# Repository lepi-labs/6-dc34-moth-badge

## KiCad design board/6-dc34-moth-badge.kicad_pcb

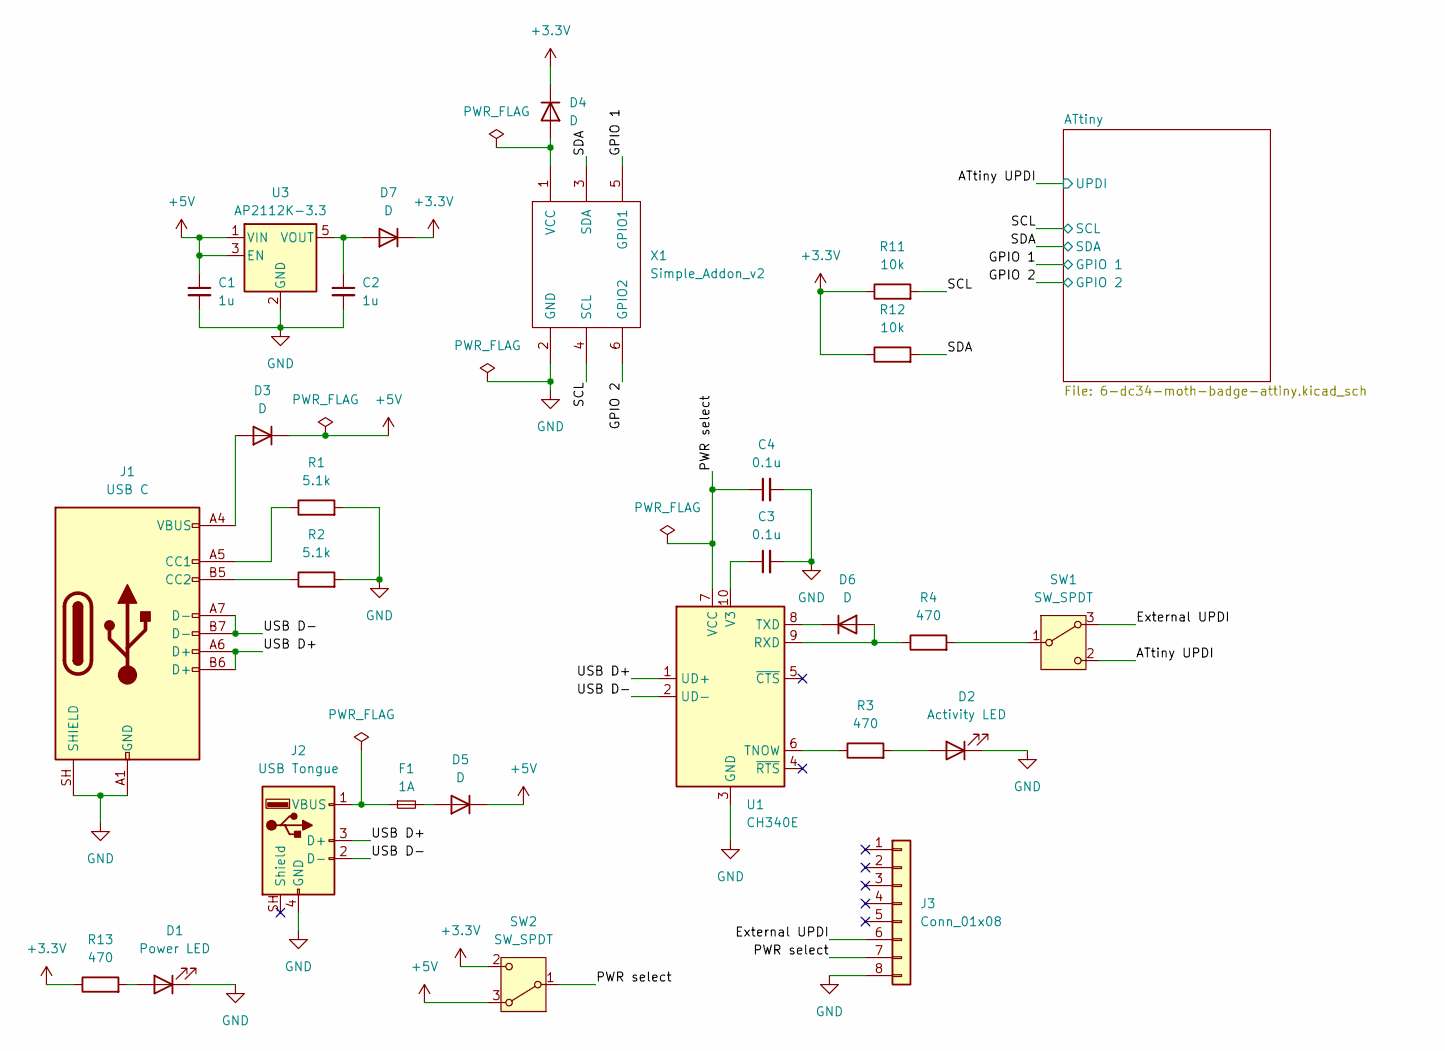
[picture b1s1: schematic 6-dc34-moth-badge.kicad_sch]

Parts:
C1, C2: 1u; C_1206_3216Metric_Pad1.33x1.80mm_HandSolder
C3, C4: 0.1u; C_1206_3216Metric_Pad1.33x1.80mm_HandSolder
D1: Power LED; LED_1206_3216Metric_Pad1.42x1.75mm_HandSolder
D2: Activity LED; LED_1206_3216Metric_Pad1.42x1.75mm_HandSolder
D3, D4, D5, D6, D7: D; D_1206_3216Metric_Pad1.42x1.75mm_HandSolder
F1: 1A; Fuse_1206_3216Metric_Pad1.42x1.75mm_HandSolder
J1: USB C; USB421603A
J2: USB Tongue; USB_Tongue
J3: Conn_01x08; PinHeader_1x08_P2.54mm_Vertical
R1, R2: 5.1k; R_1206_3216Metric_Pad1.30x1.75mm_HandSolder
R3, R4, R13: 470; R_1206_3216Metric_Pad1.30x1.75mm_HandSolder
R11, R12: 10k; R_1206_3216Metric_Pad1.30x1.75mm_HandSolder
SW1, SW2: SW_SPDT; SLW882292SMTTR
U1: CH340E; MSOP-10_3x3mm_P0.5mm
U3: AP2112K-3.3; SOT-23-5
X1: Simple_Addon_v2; Simple_Addon_v2-SAO-2x3

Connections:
+3.3V: D4.1 (K), D7.1 (K), R11.1, R12.1, R13.1, SW2.2 (C); also elsewhere on the board
+5V: C1.1, D3.1 (K), D5.1 (K), SW2.3 (A), U3.1 (VIN), U3.3 (EN)
/ATtiny UPDI: SW1.2 (C); also elsewhere on the board
/External UPDI: J3.6, SW1.3 (A)
/GPIO 1: X1.5 (GPIO1); also elsewhere on the board
/GPIO 2: X1.6 (GPIO2); also elsewhere on the board
/PWR select: C4.1, J3.7, SW2.1 (B), U1.7 (VCC)
/SCL: R11.2, X1.4 (SCL); also elsewhere on the board
/SDA: R12.2, X1.3 (SDA); also elsewhere on the board
/USB D+: J1.A6 (D+), J1.B6 (D+), J2.3 (D+), U1.1 (UD+)
/USB D-: J1.A7 (D-), J1.B7 (D-), J2.2 (D-), U1.2 (UD-)
GND: C1.2, C2.2, C3.2, C4.2, D1.1 (K), D2.1 (K), J1.A1 (GND), J1.A12 (GND), J1.B1 (GND), J1.B12 (GND), J1.SH (SHIELD), J2.4 (GND), J3.8, R1.2, R2.2, U1.3 (GND), U3.2 (GND), X1.2 (GND); also elsewhere on the board
unnamed: D1.2 (A), R13.2
unnamed: D2.2 (A), R3.2
unnamed: D3.2 (A), J1.A4 (VBUS), J1.A9 (VBUS), J1.B4 (VBUS), J1.B9 (VBUS)
unnamed: D4.2 (A), X1.1 (VCC)
unnamed: D5.2 (A), F1.2
unnamed: D6.2 (A), R4.1, U1.9 (RXD)
unnamed: D6.1 (K), U1.8 (TXD)
unnamed: C2.1, D7.2 (A), U3.5 (VOUT)
unnamed: J1.A5 (CC1), R1.1
unnamed: J1.B5 (CC2), R2.1
unnamed: F1.1, J2.1 (VBUS)
unnamed: R4.2, SW1.1 (B)
unnamed: R3.1, U1.6 (TNOW)
unnamed: C3.1, U1.10 (V3)

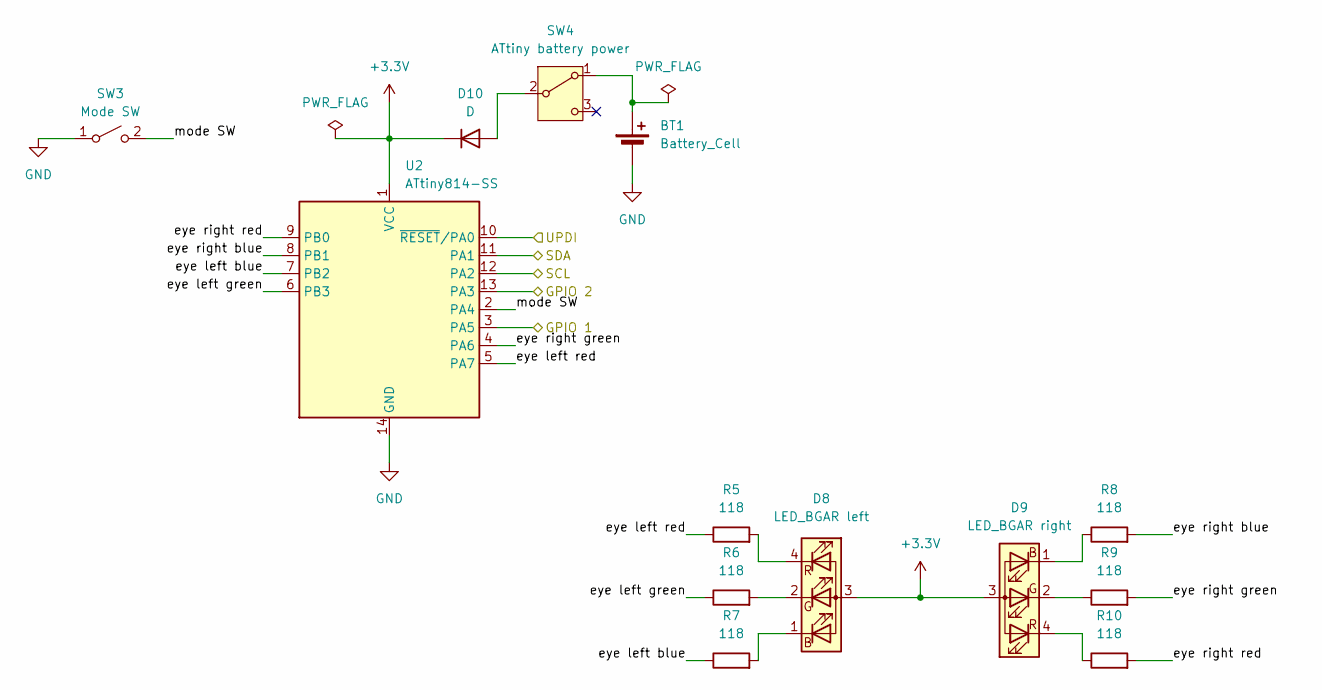
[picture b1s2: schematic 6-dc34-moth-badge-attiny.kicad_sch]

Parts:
BT1: Battery_Cell; BATHLD001
D8: LED_BGAR left; KRTBAILMS1A2872
D9: LED_BGAR right; KRTBAILMS1A2872
D10: D; D_1206_3216Metric_Pad1.42x1.75mm_HandSolder
R5, R6, R7, R8, R9, R10: 118; R_1206_3216Metric_Pad1.30x1.75mm_HandSolder
SW3: Mode SW; PHAP3344CR
SW4: ATtiny battery power; SLW882292SMTTR
U2: ATtiny814-SS; SOIC-14_3.9x8.7mm_P1.27mm

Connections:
+3.3V: D8.3 (A), D9.3 (A), D10.1 (K), U2.1 (VCC); also elsewhere on the board
/ATtiny UPDI: U2.10 (~RESET/PA0); also elsewhere on the board
/ATtiny/eye left blue: R7.1, U2.7 (PB2)
/ATtiny/eye left green: R6.1, U2.6 (PB3)
/ATtiny/eye left red: R5.1, U2.5 (PA7)
/ATtiny/eye right blue: R8.2, U2.8 (PB1)
/ATtiny/eye right green: R9.2, U2.4 (PA6)
/ATtiny/eye right red: R10.2, U2.9 (PB0)
/ATtiny/mode SW: SW3.2 (B), U2.2 (PA4)
/GPIO 1: U2.3 (PA5); also elsewhere on the board
/GPIO 2: U2.13 (PA3); also elsewhere on the board
/SCL: U2.12 (PA2); also elsewhere on the board
/SDA: U2.11 (PA1); also elsewhere on the board
GND: BT1.2 (-), SW3.1 (A), U2.14 (GND); also elsewhere on the board
unnamed: BT1.1 (+), SW4.1 (A)
unnamed: D8.1 (BK), R7.2
unnamed: D8.2 (GK), R6.2
unnamed: D8.4 (RK), R5.2
unnamed: D9.1 (BK), R8.1
unnamed: D9.2 (GK), R9.1
unnamed: D9.4 (RK), R10.1
unnamed: D10.2 (A), SW4.2 (B)

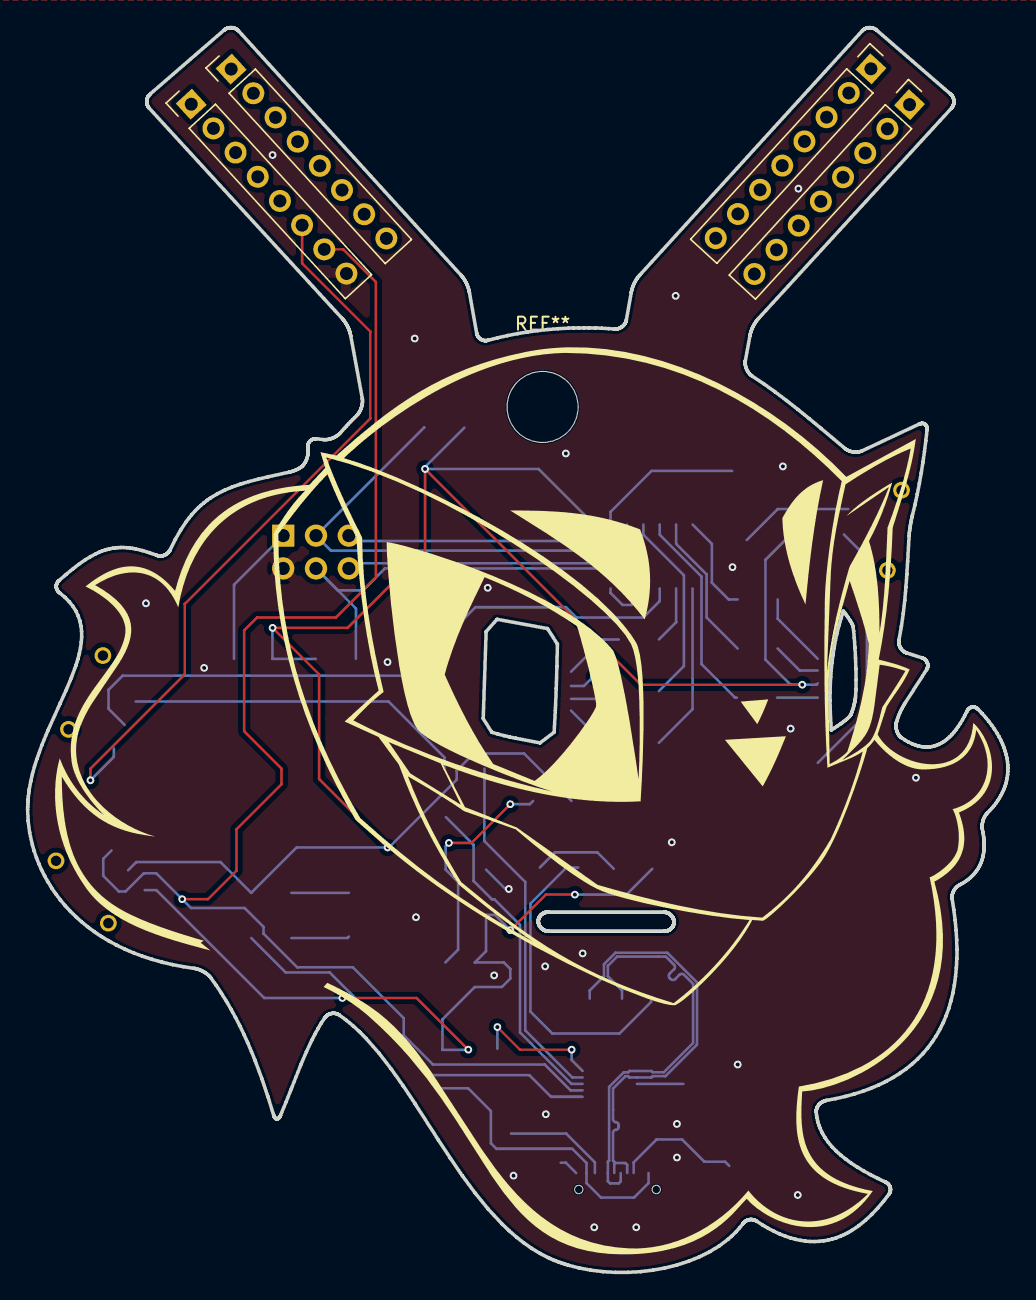
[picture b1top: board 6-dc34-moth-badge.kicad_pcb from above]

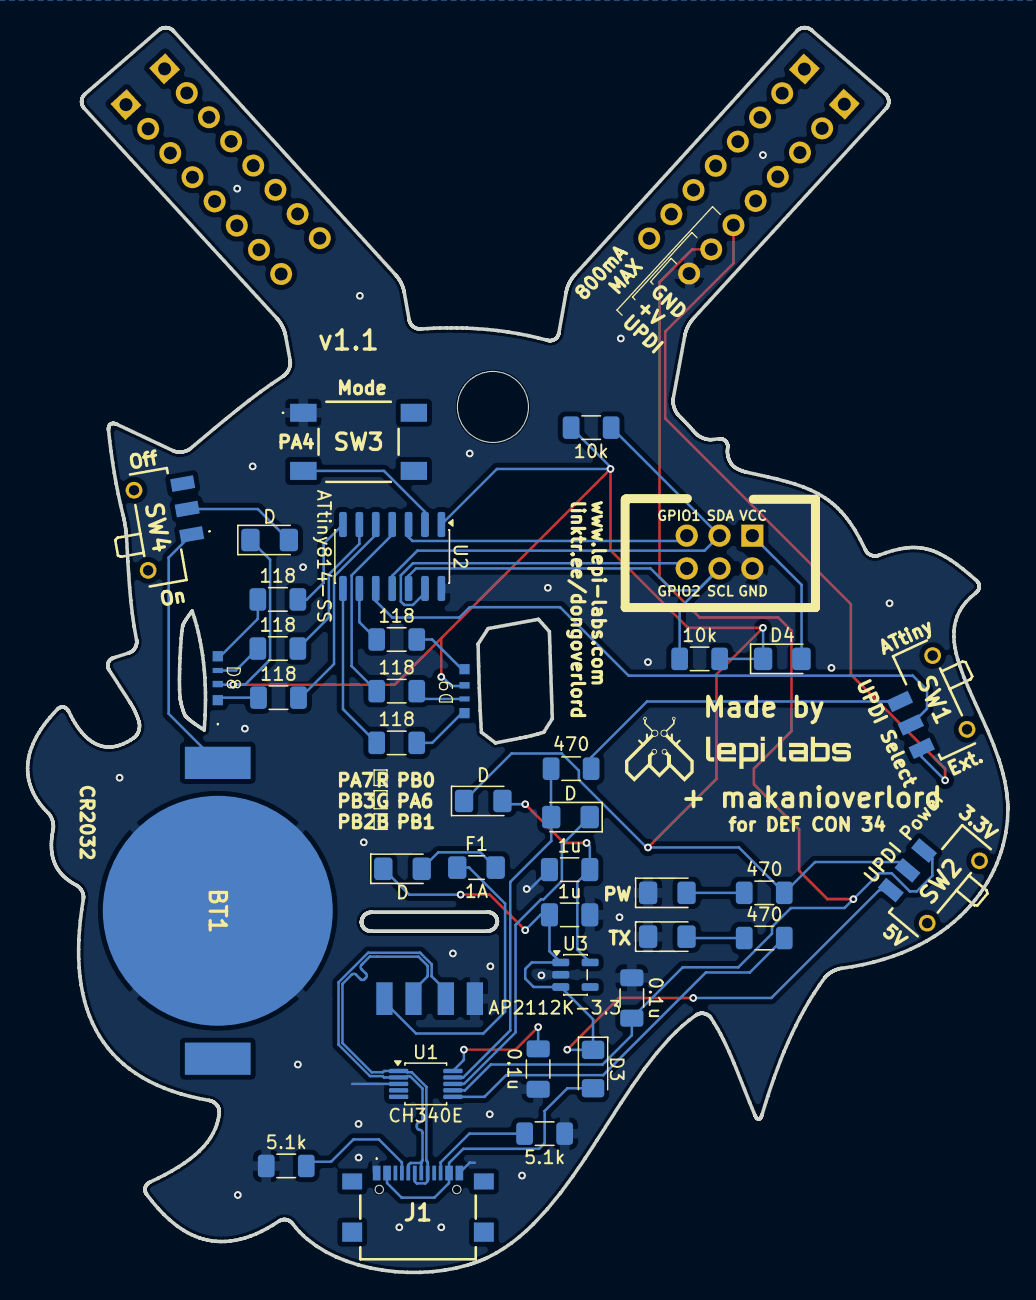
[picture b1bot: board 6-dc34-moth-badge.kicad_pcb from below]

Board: 2 copper layers, 75.9 x 96.3 mm, 40 parts (38 on the bottom side), 41 nets.

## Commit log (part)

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2026-05-23 rough draft of schematic
2026-06-09 board v0.1
2026-06-09 board art
2026-06-09 tongue board
